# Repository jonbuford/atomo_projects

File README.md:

# atomo_projects
Projects built using the Atomo System.

This is a place to share things built using Atomo. It is a combination of hardware and software, all open for reuse. 

See http://atomosys.com for system components and support.

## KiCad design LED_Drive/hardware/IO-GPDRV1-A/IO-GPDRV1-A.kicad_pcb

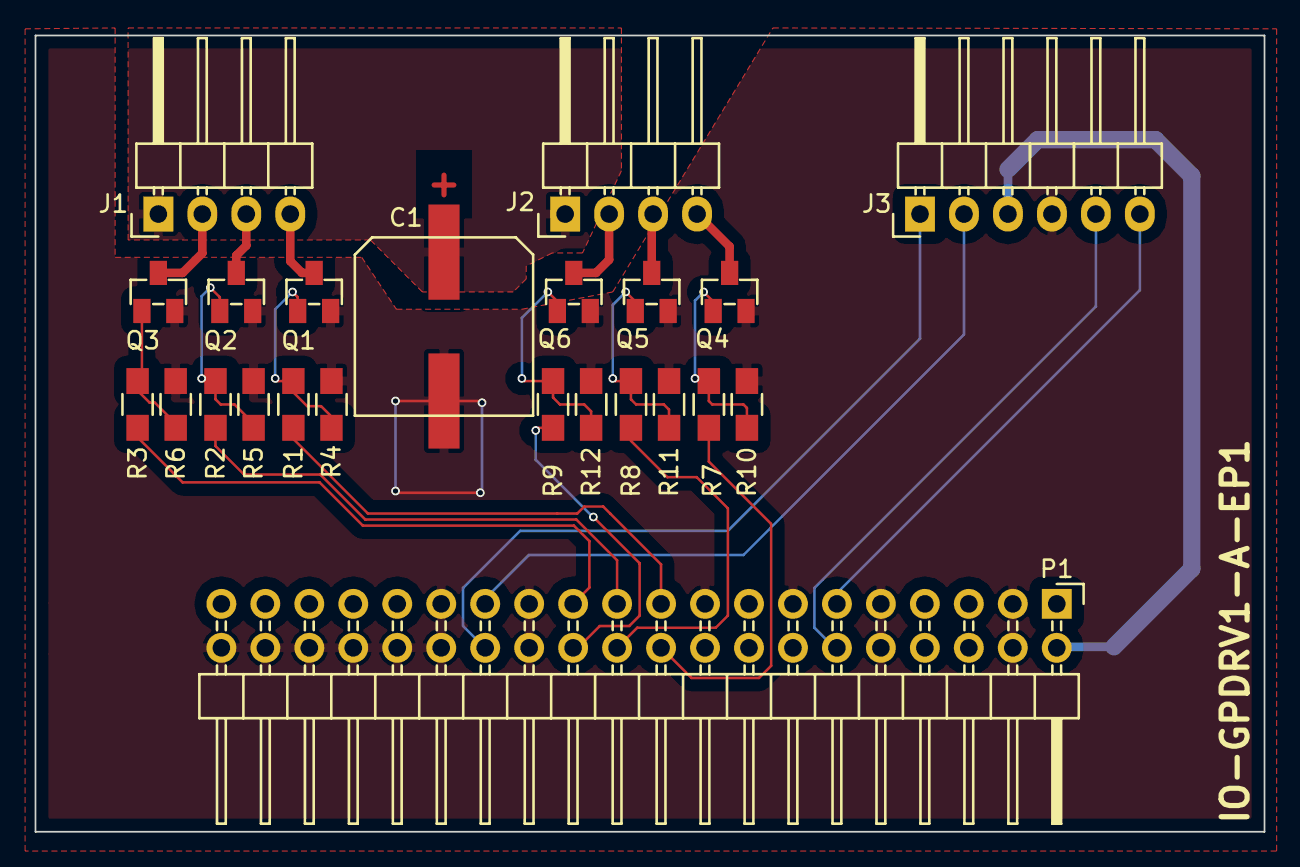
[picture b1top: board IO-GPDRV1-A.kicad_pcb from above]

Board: 2 copper layers, 71.0 x 46.0 mm, 23 parts (0 on the bottom side), 25 nets.

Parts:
C1: 100UF; Cap_Panasonic_HA-G
J1, J2: PH1X4RAFL; Pin_Header_Angled_1x04
J3: PH1X6RAFL; Pin_Header_Angled_1x06
P1: OCX40; Pin_Header_Angled_2x20
Q1, Q2, Q3, Q4, Q5, Q6: PMV40UN2; SOT-23
R1, R2, R3, R7, R8, R9: 22R; R_0805_HandSoldering
R4, R5, R6, R10, R11, R12: 10K; R_0805_HandSoldering

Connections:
/ADC0: J3.2, P1.27
/ADC1: J3.1, P1.28
/DRIVE0_A: J1.4, Q1.3
/DRIVE0_A_SIG: P1.19, R1.2
/DRIVE0_B: J1.3, Q2.3
/DRIVE0_B_SIG: P1.21, R2.2
/DRIVE0_C: J1.2, Q3.3
/DRIVE0_C_SIG: P1.23, R3.2
/DRIVE1_A: J2.4, Q4.3
/DRIVE1_A_SIG: P1.20, R7.2
/DRIVE1_B: J2.3, Q5.3
/DRIVE1_B_SIG: P1.22, R8.2
/DRIVE1_C: J2.2, Q6.3
/DRIVE1_C_SIG: P1.24, R9.2
/DRIVE_VIN: C1.1, J1.1, J2.1, P1.33, P1.35, P1.37, P1.39
/I2C_SCL: J3.5, P1.12
/I2C_SDA: J3.6, P1.11
/P3V3: J3.3, P1.2
GND: C1.2, J3.4, P1.3, P1.4, P1.9, P1.10, P1.13, P1.17, P1.18, P1.25, P1.26, P1.29, P1.30, P1.32, P1.34, P1.36, P1.38, P1.40, Q1.2, Q2.2, Q3.2, Q4.2, Q5.2, Q6.2, R4.1, R5.1, R6.1, R10.1, R11.1, R12.1
unnamed: Q1.1, R1.1, R4.2
unnamed: Q2.1, R2.1, R5.2
unnamed: Q3.1, R3.1, R6.2
unnamed: Q4.1, R7.1, R10.2
unnamed: Q5.1, R8.1, R11.2
unnamed: Q6.1, R9.1, R12.2

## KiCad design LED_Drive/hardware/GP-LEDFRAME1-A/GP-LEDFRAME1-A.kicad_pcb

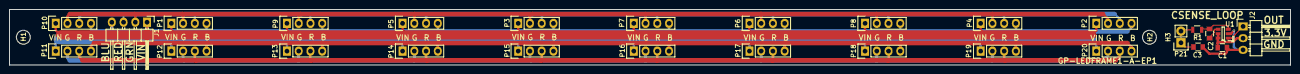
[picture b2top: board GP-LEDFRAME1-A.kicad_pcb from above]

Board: 2 copper layers, 277.0 x 12.0 mm, 31 parts (0 on the bottom side), 14 nets.

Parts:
C1: 0.1UF; C_0805
C2: Cs; C_0805
C3: Cx; C_0805
H1, H2: 3mm_Mounting_Hole; NPTH_3mm_ID
H3: 8mm Slot; 8mm_slot
J1: PH1X4RAFL; Pin_Header_Angled_1x04
J2: PH1X3RAFL; Pin_Header_Angled_1x03
P1, P2, P3, P4, P5, P6, P7, P8, P9, P10, P11, P12, P13, P14, P15, P16, P17, P18, P19, P20: 1X4_LED_PADS; Pin_Header_Straight_1x04
P21: CONN_01X02; Pin_Header_Straight_1x02
R1: R; R_0805
U1: AT42QT1011; SOT-23-6

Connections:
/ADC0: J2.1, U1.1
/DRIVE0_A: J1.4, P1.4, P2.4, P3.4, P4.4, P5.4, P6.4, P7.4, P8.4, P9.4, P10.4
/DRIVE0_B: J1.3, P1.3, P2.3, P3.3, P4.3, P5.3, P6.3, P7.3, P8.3, P9.3, P10.3
/DRIVE0_C: J1.2, P1.2, P2.2, P3.2, P4.2, P5.2, P6.2, P7.2, P8.2, P9.2, P10.2
/DRIVE_VIN: J1.1, P1.1, P2.1, P3.1, P4.1, P5.1, P6.1, P7.1, P8.1, P9.1, P10.1
/P3V3: C1.1, J2.2, U1.5, U1.6
GND: C1.2, C3.2, J2.3, U1.2
unnamed: C2.1, R1.2, U1.3
unnamed: C2.2, U1.4
unnamed: C3.1, P21.1, P21.2, R1.1
unnamed: P11.1, P12.1, P13.1, P14.1, P15.1, P16.1, P17.1, P18.1, P19.1, P20.1
unnamed: P11.2, P12.2, P13.2, P14.2, P15.2, P16.2, P17.2, P18.2, P19.2, P20.2
unnamed: P11.3, P12.3, P13.3, P14.3, P15.3, P16.3, P17.3, P18.3, P19.3, P20.3
unnamed: P11.4, P12.4, P13.4, P14.4, P15.4, P16.4, P17.4, P18.4, P19.4, P20.4

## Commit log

2017-02-19 Updating .gitignore to include KiCAD files.
    Adding the extended ignore before adding the first project files here to prevent them from being added in the first place. Missed this with the other repo and it is a bit of a pain.
2017-02-19 Initial commit of project files
    Adding firmware and board designs. The firmware is a known good build
    that would be suitable for a basic GPIO test of the controller. It could
    be ported to others easily, but the pin definition is for the
    CM-164K64-A version. I'll add the pin and clock Kinetis tool files in a
    separate directory to include other configurations.
    The project is built from the ground up using KDS SDK V3.2.0 generated
2017-02-20 Eclipse workspace - Added project
    This is using a workspace at the top level and imported the existing
    projects (LED_Driver).
2017-02-20 Creating Readme
    Initial Readme commit.
2017-02-20 Revert "Eclipse workspace - Added project"
    This reverts commit fefdbd2be6aeebafea6a850540ec51c5c80ffbac.
2017-02-20 Adding some additional ignore for Eclipse
2017-02-20 adding ignore settings
2017-02-20 Updating Eclipse ignores
    Trying to take care of sub-directories.
2017-02-20 Seeing if we can clean up the Eclipse files.
2017-02-20 .cproject
    Not sure if we will add this ignore as well.
2017-02-21 Addding copy of existing firmware as a separate test firmware
    Just getting this stuff sorted on how to organize it best. I'm copying
    the existing firmware over to a test folder to keep it for a basic test
    app, so it is easy to maintain. Initially I was thinking there is
    separate branches or whatever, but that doesn't work well since you end
    up having to sync to a particular branch to work on it. This way it is
    all in one repo. Not sure if all projects will be set up this way or if
2017-04-04 Delete BSilk.kicad_mod
    This is a production file from another product using the Atomo logo currently and is not part of the open source distribution files.
2017-04-04 Delete FSilk.kicad_mod
    This is a production file from another product using the Atomo logo currently and is not part of the open source distribution files.
